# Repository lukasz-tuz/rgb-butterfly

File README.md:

# 🦋 Butterfly LED Panel: Smart Light for ESPHome

- [🦋 Butterfly LED Panel: Smart Light for ESPHome](#-butterfly-led-panel-smart-light-for-esphome)
  - [Supplies](#supplies)
  - [Concept and Design Considerations](#concept-and-design-considerations)
  - [Shaping the Butterfly](#shaping-the-butterfly)
  - [CAD](#cad)
    - [3D Modelling](#3d-modelling)
    - [Placing the LEDs](#placing-the-leds)
  - [Controller](#controller)
    - [Schematic and PCB](#schematic-and-pcb)
    - [Connectors](#connectors)
    - [Housing](#housing)
  - [Assembly](#assembly)
    - [Manufacturing](#manufacturing)
    - [Preparations](#preparations)
    - [Soldering](#soldering)
    - [Connector](#connector)
    - [Diffusing the light](#diffusing-the-light)
  - [Making The Panel Touch Sensitive](#making-the-panel-touch-sensitive)
  - [Software](#software)
    - [Substitutions](#substitutions)
    - [ESPHome configuration](#esphome-configuration)
    - [API and interfaces](#api-and-interfaces)
    - [Peripherals configuration](#peripherals-configuration)
    - [Lights](#lights)
    - [Touch controls](#touch-controls)
  - [Final Thoughts](#final-thoughts)

I've always been a fan of light panels, at least ever since I first saw
[Nanoleaf's products](https://nanoleaf.me/). My apartment has slanted walls, and
it's always been an issue to light it properly. Nanoleaf light panels got the
job done, but one place left without proper lighting: kid's bed, right
underneath a slanted wall.

At first I figured I'd just pay up and buy more light panels. But she's such a
big fan of butterflies - already had tons of stickers on that wall. Then it
struck me: I could make her a butterfly-shaped light panel to serve as a night
light. So, here goes.

## Supplies

Full bill of materials, with prices (in PLN, sorry), is attached. It includes
full BOM for PCB, including  [LCSC](https://lcsc.com/)  part numbers, estimated
prices, etc.

In addition to the PCB and its components, you'll need:
- 3D printed frame
- 3D printed case for controller
- plexi, 3 mm thick, white (laser cut is best)
- plexi, 2 mm thick, frosted (laser cut is best)
- plexi, 3 mm thick, black (laser cut is best)
- 5V 8A power supply with 2.1 mm DC jack plug
- WS2813 LED strip, 144 LED/m (different LED models can be used as well)
- Conductive PET sheet:
  https://kamami.pl/en/conductive-materials/563060-conductive-pet-ito-with-dimensions-100mm-x-200mm.html
- 4x1 Goldpin header
- DC barrel jack socket, 2.1 mm
- (optional) TE-Connectivity 1-1954289-2 connectors:
  https://www.arrow.com/en/products/1-1954289-2/te-connectivity
- some baking paper
- lots of wires, including 22AWG or similar
- general purpose glue

I estimate total cost of materials above to ~$110 USD, with the current exchange
rate.

## Concept and Design Considerations

I wanted the panel to have sections which could be individually lit to form of a
[low poly
butterfly](https://www.google.com/search?q=low+poly+butterfly&client=opera&hs=mmj&sxsrf=APq-WBtdjmTwirM-b7sVY4Ri69_1T6-vsw:1650900132022&source=lnms&tbm=isch&sa=X&ved=2ahUKEwjdtbafwq_3AhXHSvEDHZS5BSMQ_AUoAXoECAEQAw&biw=2061&bih=1141&dpr=1)
(I really like the low poly aesthetics). I also assumed use of a cut down LED
strip, to save time and money on custom PCBs, and ESP32 as a controller for the
lights, because I wanted to use  [ESPHome](https://esphome.io/)  for controlling
the lights and integrating into Home Assistant setup. I also wanted these panels
to be controllable locally (i.e., without having to use smartphone), ideally by
making the panels touch sensitive.

With these design constraints there are several options, choices to be made for
	the design: - use analogue RGB/RGBW strips vs. addressable ones - have the
	light built from multiple small panels vs. few larger ones, divided into
	segments

There are some serious cons to using analogue strips, especially given the
constrains: typical analogue LED strip needs it's own PWM driver for each
channel. This makes routing connections way more difficult and also pretty much
breaks the "save time and money on custom PCBs" assumption. Assuming use of
multiple panels, it would take a few dozen panels to create a low poly
butterfly. Total number of PWM signals would exceed number of PWM outputs in
ESP32. To mitigate, each panel would have to have its own micro-controller,
which would use a communication bus to receive commands from the controller.

In short, too complicated and bumps up the cost of each panel. Summarizing:
1.  analogue LED strip/many panels:
2.  needs custom PCB with LED drivers and separate uC per panel
3.  analogue LED strip/few panels
4.  still needs lots of LED drivers and custom PCB, slightly easier to route
    connections than 1st one
5.  addressable LEDs/many panels
6.  increased cost of 3D printing cases for panels, but only one wire needed to
    control all the LEDs
7.  addressable LEDs/few panels
8.  well... this could work.

There are so many different addressable LED strips available, it's difficult to
pick one. I decided to go with a dense strip (144 LEDs/m) based on WS2813
devices. Downside is that this strip has a rated power consumption of 43W/m. So,
a lot of current to supply at 5V...

That's how my smart light ended up having two separate panels (wings!) and
controller in the middle. But what about the low poly part? It's difficult to
get the low poly effect with just two panels. Luckily, in one of my other
projects I noticed that LED lights can be nicely partitioned. More on that
later.

## Shaping the Butterfly

For the silhouette of the butterfly, I went to trusty
[openclipart.org](http://openclipart.org/)  library. Found  [Monarch
butterfly](https://openclipart.org/detail/224784/monarch-butterfly)
cliparclip-artt, wonderful shape with decent amount of space for placing all the
LEDs. A bit of Inkscape magic, and I got the raw silhouette of a butterflies'
wing. I scaled it so that it would have diagonal of ~20 cm. I also modified the
shape a bit so that it has a distinct straight edge to which controller could
attach.

This created the outer edge of the panel. Two additional paths will be needed
later: one for marking where the internal support for panel's cover starts, and
the other is an inner edge. This can be done by cloning and shrinking the
initial shape. Best to keep approx. 2 mm of separation between the outlines.

For the whole low poly thing, I used Inkscape's Effects tool to generate a
[Voronoi diagram](https://en.wikipedia.org/wiki/Voronoi_diagram)  within the
constraints of inner edge. While low poly structures are typically composed of
triangles, this pattern gets the job done, as well.

## CAD

### 3D Modelling

Completed SVG now can be used to quickly start with 3D modelling. I'm using
[FreeCAD](https://www.freecadweb.org/), but any tool will do. You'll find
FreeCAD file in here:  https://github.com/lukasz-tuz/lowpolylight-cad.

First step is to extrude panel outline, by 3 mm, to form a back plate of the
panel. This part could be 3D printed, but I ordered it as a laser-cut white
plexiglass, opaque. It tends to be cheaper than 3D printing, and creates a
smoother shapes.

Next part is the side wall. Side wall contains a small cut, 2 mm deep, roughly
1.5 mm wide, which will be used to support front panel. That's where the inner
edges from SVG come in handy: extrude outer edge (12 mm should be enough space
to diffuse light from LEDs), extrude middle edge by 2 mm, and subtract.

Wall also should have a small cutout on a side for connecting to the controller.

Once wall is ready, it's time for the Voronoi pattern. This actually takes some
manual drawing. Pattern imported from SVG is handy, but can't be directly
extruded as all the lines are one dimensional. FreeCAD's sketching tool helps
here, but care has to be taken to ensure that the pattern overlaps with walls.
It won't be possible to print this part, otherwise.

Note the 6 mm gap between lower edge of pattern walls and back of the panel.
This way pattern walls block some of the light of LEDs inside a partition,
creating nice effect of a light segment.

Finally, front cover is created by extruding the inner edge from SVG. This part
could also be 3D printed (standard resin would do nicely), but again, I used
laser-cut plexi, 2 mm, this time with 30% opacity.

Design parts have to be cloned by mirroring to form a second wing.

### Placing the LEDs

It's all fun, 3D models for wings are ready, but how many LEDs will  *actually*
fit in there?

I wanted each segment in the Voronoi pattern generating enough light so that
this panel would be a usable light source, but at the same time, it'd be best to
try and limit current drawn by the diodes.

I ended up placing 65 LEDs per wing, and frankly, I overdid it. Whole thing
would still work with half the amount of LEDs. Oh well.

Some numbers:

- 65 LEDs per wing, total of 130 in the panel.
- with 144 LEDs per meter, 43 Watts power draw per meter, single LED consumes
  **~0.3 W at 5V**
- 130 LEDs would consume  **39 Watts**.

These numbers will be needed for the next step.

<script src="https://embed.github.com/view/3d/lukasz-tuz/rgb-butterfly/main/docs/lowpoly-butterfly.stl"></script>

## Controller

### Schematic and PCB

At first, full disclaimer: power delivery part of the controller could've (and
should've) been done better. Right now it's a very simple device, merged from
application notes for ESP32 and the voltage stabilizer.

Controller is built around ESP32 IoT module - ESP32-WROOM. These modules are
affordable, yet capable, and easy to obtain. Following typical application
circuit from ESP32-WROOM's datasheet:

- two capacitors (C5, C7; 100nF and 22uF) are filtering the 3.3V supply
- two capacitors filter the 'EN' pin; this pin is also pulled up to 3.3V by 10k
  resistor
- push button SW1 connects 'EN' pin to ground, forcing it to reset
- push button SW2 is used as boot mode selector (holding SW2 while pressing SW1
  makes the module fetch code from serial port)

Power to the module is provided by a single AMS1117-3.3 voltage stabilizer. This
device is ubiquitous, can be found on almost all low-cost development boards for
ESP. Few capacitors connect input and output of the device to ground.
AMS1117-3.3 is internally wired to output a 3.3V, so no additional resistors are
required. Input to the stabilizer comes directly from 5V power supply.

Given the power-hungriness of selected diodes, PCB traces which supply power to
the panels are pretty thick - 2 mm, with 0.8 mm min distance from other nets.
Given the current (up to 8 amps!), this net should've been even thicker, or
divided into two separate ones.

### Connectors

Given the amount of current which could potentially flow to the LEDs, connection
between controller and panels really should not be done by your run of the mill
goldpins. XST connectors typically used for LED strips would do the trick, but
are too bulky to be of use here.

Took some digging, but I finally found  [TE Connectivity
1-1954289-2](https://www.arrow.com/en/products/1-1954289-2/te-connectivity),
which is perfect for the job. 4 pins are needed:

- +5V
- ground
- LED control line
- touch sensors

Note that the cutout in panel's wall is just big enough to house this connector.

There's also a standard issue gold pin connector for serial port. Ground and
+3.3V nets are routed to that connector, so any type of USB-to-serial converter
can be used. Just make sure to not connect +5V to the +3.3V pin of the serial
port header. ESP32 will probably survive but no point in taking chances.

> However, soldering wires instead using some exotic connector will work just as
> fine.

### Housing

Now, back to drawing board. Err, CAD. Controller can't just hang there between
the panels, it needs a casing. Since - as usual - I rushed PCB design and forgot
about mounting holes, I decided to design a very simple 3D printed case in which
the PCB would rest, held in place by connectors. Cover for the case is laser cut
plexi, black this time, in shape of butterfly's body. Cover is wider and longer
than the case itself, so it hides all connectors.

Case has also small rectangular cutouts in which case fits. Cutouts are slightly
(0.1 mm) smaller in each direction than the mounting pins on the case, so it
doesn't really need any glue or screws.

## Assembly

### Manufacturing

I ordered the laser-cut and 3D-printed parts at
[ajmaker.pl](http://ajmaker.pl/), they offer good quality with reasonable prices
(and I am not affiliated with them in any way, I just buy stuff from them :)).

Note on 3D printing the side wall/Voronoi pattern: make sure to use material
with the highest temperature resistance you can find. LEDs can get hot!

Controller's PCB (including SMT assembly) was made by
[JLCPCB](https://www.jlcpcb.com/see), I highly recommend their services. It's
super easy to place the order using their online interface - just add gerber
files (live preview!), select options for the PCB - base material, number of
layers, color (purple PCB, anyone?), thickness, etc. - add to cart and done. If
anything's wrong or not clear, their engineers will contact you to resolve
things. SMT service is great as well. Lots and lots of parts in stock so it's
easy to find matching devices.

Once all the parts arrive, it's time for some assembly.

### Preparations

First step here is to cut the LED strip into fragments matching the CAD design
and arrange them on the back plate of the panel. When arranging, make sure that
LED strip fragments are arranged so that ground and power supply pins are next
to each other in adjacent fragments. Otherwise laying down the wires will get
complicated. Fragments of the LED strip can be glued to the back plate at this
point, it'll make soldering bit easier later on.

### Soldering

Even though its cut down, it still is a LED strip. Addressable LEDs use just one
wire (in case of WS2813 diodes I used - two wires, additional wire serves as
backup) for control, but all devices need to be connected in chain on the same
wire. So, it is important arrange and solder all the LED fragments as a chain,
avoiding any loops. At least on the control pins.

For connecting power and ground pins of LED strip fragments I used standard
22AWG wire ([this
one](https://thepihut.com/products/prototyping-wire-spool-set), to be exact).
Soldering it to the LED strip was sometimes bit difficult, but at least it can
withstand high current and not melt... It's also pretty rigid, so it also helps
to keep all the LED strip pieces in desired places.

For signal lines, any wire will do. I used thin wire stripped off from a tape;
easy to work with and easy to solder.

### Connector

Once all the LEDs are in place and all the wires are soldered, it's time for the
connector. TE part I picked is meant for SMT soldering, but it has large pads.
It's super easy to solder wires to it. Make sure you're soldering them in the
right order: power supply and ground on the outer pins, signal lines on the
inner.

I found (by trial and error, obviously) that using more elastic wires for
power/ground than 22AWG makes it easier to assemble everything later on.

One of the signal pins needs to be connected to the LEDs, the other should be
left dangling for the touch sensor. I left around 5-7 cm piece of wire with
approx. 1 cm with removed isolation. This wire is supposed to connect to a
conductive layer (added in next steps) to form a touch sensor.

At this point it should be safe to assemble back plate with the wall/partition
part. I used general purpose glue based on polyurethane-elastomers. It's
transparent, creates an elastic bond, and does not dry immediately which gives
an opportunity for adjusting alignment of parts. Also, as it turns out, if you
need to disassemble a glued part, just cut through the glue with a scalpel,
scrub out remains of the old bond, and glue again.

> I do not recommend using cyanoacrylate-based glues (e.g., Super Glue). They
> can dissolve 3D-printed parts.

### Diffusing the light

Front of the panel is made of frosted, 30% opacity Plexiglas, which diffuses the
light on its own. First startups of an assembled panel show, however, that the
diffusion effect is not strong enough.

There's a boatload of guides on the internet on how to diffuse light of a LEDs.
After some experimenting with what I had on hand, I went with baking paper. It
can easily be cut to desired shape, diffuses the light nicely, and is heat
resistant (which is good, because the diodes can get quite hot). So, cut two
butterfly wing-shaped pieces out of baking paper sheet (use front panel part as
template), and place them on the walls of the Voronoi pattern part. Just that,
no need to glue it, pin it, or anything. Front plexi will go on top of it and
will hold it down in place.

## Making The Panel Touch Sensitive

Remember the dangling wire soldered to wing connectors? Now it's time to put it
to work.

My first approach was to use  [conductive
paint](https://www.bareconductive.com/)  to paint the Voronoi pattern on top of
the front plexi. Idea was that loose end of the wire would be painted over and
held in place by the paint. That did not work because conductive paint does not
stick to plexi. I used paper tape to mask the lines and when I pulled the tape
off, conductive paint decided to stick with the tape rather than the panel.

Second approach, was to use silver adhesive, conductive tape to lay out Voronoi
pattern on top of the front cover. Touch sensor wire would be connected outside
of the panel, but simply one of the pattern's edges extended to inner side of
the front cover, where it was wrapped over the touch sensor wire.

This was a limited success (see video above); touch controls worked, but there
were constant problems with maintaining electrical connection between segments
in the pattern. Also, visual effect wasn't exactly what I hoped it would be.

So after some digging around the interwebs I found transparent,  [conductive
plastic
sheet](https://kamami.pl/en/conductive-materials/563060-conductive-pet-ito-with-dimensions-100mm-x-200mm.html).
It's easy to cut and provides additional diffusion of light. Once cut, can
simply be placed on top of the baking paper, err.. light diffuser. Stripped
fragment of the touch sensor wire should be placed on top of the conductive
layer (can be taped, but I didn't bother), and front cover placed directly on it
and glued to the walls.

And that's it, panel is now touch sensitive.

## Software

Software for the controller is built on top of the
[ESPHome](https://esphome.io/)  framework. Everything is captured in a short
YAML configuration file. Let's go over each section of the configuration.

### [Substitutions](https://esphome.io/guides/configuration-types.html?highlight=substitutions#substitutions)

```yaml
substitutions:
  name: "kids-room-bedlight"
  num_leds: '66'
  max_led_idx: '65'
  gamma_correct: '1.5' 
```

These definitions hold values which are use in several places throughout the
configuration. To make it easier to tweak those values, it's good to have them
defined in one place. Basic, run-of-the-mill constants for:

- *name*: name of the device which will be used as host name, as well as Home
  Assistant entity for the light. Here it's "Kid's room bed light" because
  that's where the panel will be placed
- *num_leds*: total number of LED diodes in the device
- *max\_led\_idx*: highest value for zero-based index of LED. Has to equal to
  *num_leds*  \- 1
- *gamma_correct*: gamma correction factor applied to lights

### ESPHome configuration

```yaml
esphome:
  name: ${name}
  project:
    name: "hexalight.lowpoly-butterfly"
    version: "1.0.0"

esp32:
  board: esp32dev
  framework:
    type: arduino

# Enable logging
logger: 
```

This section contains basic configuration of the  [ESPHome framework
itself](https://esphome.io/devices/esp32.html). See how previously defined
device name is used, using `${name}` syntax?

Project section allows for defining manufacturer (yeah, I know :D) and model
name, as well as version.

"esp32" defines values needed for [PlatformIO](https://platformio.org/)
framework on which ESPHome is built upon. Selects board type and low-level
firmware framework - operating system and set of libraries to use. In this case,
Arduino is used to fuel the code.

### API and interfaces

```yaml
# Enable Home Assistant API
api:

ota:
  password: !secret ota_password

wifi:
  ssid: !secret wifi_ssid
  password: !secret wifi_password

# Enable fallback hotspot (captive portal) in case wifi connection fails
ap:
  ssid: "Lowpoly-Butterfly"
  password: !secret ap_password

captive_portal:
```

This part enables ESPHome awesomeness:

- *api*: adds support for the  [Home Assistant](https://www.home-assistant.io/)
  interface, making the device magically appear in the home automation
- *ota*: enables Over-the-air firmware updates. Only first programming needs to
  be done using serial interface, any subsequent update will go through Wi-Fi
- *wifi*: turns on Wi-Fi stack, allowing the device to connect to network
  specified by  *ssid*  using provided  *password*
- *ap:* enables fallback hotspot, AKA captive portal. If connection to selected
  network fails, device will set up its own hotspot, using  *ssid*  and
  *password*  provided here
- *captive_portal*: (requires enabled access point); when Wi-Fi connection
  fails, device will display a web page to re-configure Wi-Fi
- *web_server*: (optional) when enabled, device will be accessible using web
  interface, allowing for remote control even without Home Assistant setup
- *esp32_improv*: (optional) when enabled, device will use ESPHome
  implementation of the  [Improv](https://www.improv-wifi.com/)  standard to
  provision ssid and password. So, no need to type them in configuration file.

Notice the "*!secret some_password*" syntax in all the places which require
providing a password. Using the "*!secret*" tag, ESPHome scripts refer to a
separate file - secrets.yaml - to look for the password. This way ESPHome config
files can be shared over the internat without exposing passwords to own Wi-Fi.
Of course that's assuming you don't file the secrets.yaml...

### Peripherals configuration

Now, configuration of ESP32's peripherals.

```yaml
switch:
- platform: restart
  name: "Restart Light" 
```

This part defines a virtual  [reset
button](https://esphome.io/components/switch/restart.html). Switch will be
visible as an entity in Home Assistant and web interface (if enabled).

- esp32\_touch: setup\_mode: false iir\_filter: 15ms low\_voltage\_reference:
  0.5V high\_voltage\_reference: 2.7V voltage\_attenuation: 1.5V
- '*esp32_touch*' enables code for  [touch sensor
  pads](https://docs.espressif.com/projects/esp-idf/en/latest/esp32/api-reference/peripherals/touch_pad.html)
  built into the ESP32 device. ESP32's touch pad peripheral continuously charges
  and discharges the touch pad (in this case - the conductive plastic sheet
  under front cover). Changes in the charge/discharge timings indicate change of
  capacity of the touch pad. And capacity of the touch pad changes when it is
  touched.
- *setup_mode*: when set to true, touch pad is in setup mode, in which results
  of the touch pad measurements are periodically printed out to the log. Useful
  when building the device, because it makes calibration of the touch pad super
  easy
- *iir_filter*: enables  [Infinite Impulse
  Response](https://en.wikipedia.org/wiki/Infinite_impulse_response)  filter to
  be applied to the touch pads. Can increase accuracy, and turned out to be
  helpful for making the touch panel work
- *low\_voltage\_reference*,  *high\_voltage\_reference*: reference values for
  voltage used by ESP32 touch pad subsystem to analyze the charge/discharge
  pattern. Used to tune the performance of touch panel
- *voltage_attenuation*: value of the voltage attenuation to use for the charge
  cycles. Based on my observations, increasing this value increases resolution
  of the touch pad, making it easier to determine a threshold for on/off values

### Lights

As probably expected, configurations related to LEDs themselves consumes most of
the configuration file. Let's go over it in steps.

```yaml
light:
  - platform: fastled_clockless
    gamma_correct: ${gamma_correct}
    restore_mode: ALWAYS_OFF
    rgb_order: GRB
    chipset: WS2813
    pin: GPIO22
    num_leds: ${num_leds}
    name: "Right Wing"
    id: right_wing
    internal: true

- platform: neopixelbus
  gamma_correct: ${gamma_correct}
  restore_mode: ALWAYS_OFF
  type: GRB
  variant: WS2813
  pin: GPIO23
  num_leds: ${num_leds}
  name: "Left Wing"
  id: left_wing
  internal: true 
```

First, we have to define low-level libraries to interact with LEDs. These map to
physical layout of the diodes. Note that two different libraries are used:
[FastLED Clockless](https://esphome.io/components/light/fastled.html)  and
[Neopixelbus](https://esphome.io/components/light/neopixelbus.html). These
libraries provide similar set of features to control addressable LEDs. Two
different are used because code wouldn't compile when the same library was used
for two separate sets of lights. Probably something related to use of global
variables, but I wasn't really inclined to debug this; perhaps another day. For
now, one library is used for left wing, the other for right wing.

Both libraries have a very similar set of configuration options:

- *platform*:  *fastled_clockless*  or  *nexopixelbus*  selects underlying
  library to use for the light entity
- *gamma_correct*: gamma correction factor to apply to this light
- *restore_mode*: defines how light should behave on power up. ALWAYS_OFF is a
  safe bet to make sure light won't randomly turn on when power comes back from
  outage or when the devices encounters a software bug and resets in the middle
  of the night
- *rgb_order*  or  *type*: defines order in which colors in LED are to be
  defined; if defined incorrectly, configuration will not match actual color
  channel, and setting values for red would change another color in the LED.
- *chipset*  or  *variant*: select model of the RGB LED diode used in the LED
  strip
- *pin*: pin in ESP32 module to which LED strip is connected
- *num_leds*: number of LEDs in connected to selected pin
- *name*: (optional) name for this light; typically, that's the name that would
  be displayed in Home Assistant
- *id*: unique identifier for the light used within the code
- *internal*: set to true means that this light will not be exposed externally,
  in Home Assistant or web interface

Logical definition uses  [ESPHome's light
partition](https://esphome.io/components/light/partition.html)  feature which
allows for merging several physical lights into single, controllable light
entity (it also allows for splitting a single physical light into several
logical ones).

Some options are common to all light entities (*name*,  *id*,  *restore_mode*,
...), so let's skip them here.

- *segments*: definition of segments used by this partition. Defines which
  physical lights and which LEDs in those lights should be used for the
  partition. Here, all diodes from both wings are selectd
- *id*: identifier of physical light
- *from*  and  *to*: range of LED  indices  to use for the segment
- *effects*: defines list of light effects (also known as scenes, animations,
  etc.) for the logical light entity
- *addressable_lambda*: uses  [*lambda
  expression*](https://en.cppreference.com/w/cpp/language/lambda)  for
  definition of an effect
- *name*: name of the effect
- *update_interval*: defines how often should the lambda expression be executed
- *lambda*: body of the lambda expression
- *addressable_rainbow*: creates effect of a floating rainbow by cycling through
  entire RGB space on each LED
- *addressable_twinkle*: randomly twinkles individual diodes, creating effect of
  blinking stars

Some effects are defined by raw C++ code. The "Reading Light" effect is simple.

```c
  it.all()= Color(255, 170, 160);
  return;
```

This sets all diodes to a specific color. I picked this color because it's easy
on the eyes, bit pinkish, and reduces strain when reading. "Voronoi" effect is
more complex. I wanted an effect which lights up each partition in the Voronoi
pattern individually, and smoothly transitions colors for each of the partition.
Also wanted to make sure that colors used will resemble an actual  [monarch
butterfly](https://www.google.com/search?client=opera&q=monarch+butterfly).
Lambda expression for this effect is evaluated every 1 ms.

```c++
  #define INT_TO_FIXED16(n) (n << 8)
  static const uint8_t nsegments = 18;
  static const uint8_t speed = 2;

  // Count of LEDs in each of the segments
  static const uint8_t segments[nsegments] = {6, 6, 5, 12, 2, 13, 3, 4, 5,\
                                              7, 6, 5, 12, 2, 13, 5, 4, 3};
  static uint16_t colors[nsegments];
  
  static const uint16_t min_hue = INT_TO_FIXED16(142);
  static const uint16_t hue_range = INT_TO_FIXED16(81);
  static const uint16_t max_hue = min_hue + hue_range;
```

Note how all the configuration constants/variables are defined as  *static*.
This keyword makes these variables persistent over subsequent evaluations.
Values set to those variables in one evaluation are kept for the next one.

```c++
  if (initial_run) {
    for (int i = 0; i < nsegments; i++) {
      // Initialize to a random color
      colors[i] = (uint16_t)(random_uint32() & 0x0000FFFF);
    }
  }
```

This code generates random target color for each partition (AKA segment) in the
Voronoi pattern.

```c++
  ESPHSVColor hsv(0, 240, 255);
  uint16_t start = 0;
  for (uint8_t i = 0; i < nsegments; i++) {
    uint16_t end = start + segments[i] + 1;
    colors[i] = (colors[i] + speed) % 0xFFFF;
    hsv.hue = (colors[i] >> 8) & 0xFF;
    it.range(start, end) = hsv.to_rgb();
    start = end;
  }
  return;
```

And finally, loop that makes gradual color transition for each partition.

### Touch controls

Touch pad controls use  [binary sensor implementation in
ESPHome](https://esphome.io/components/binary_sensor/esp32_touch.html).

```yaml
  binary_sensor:
  - platform: esp32_touch
    name: "On/Off"
    pin: GPIO32
    threshold: 1150
    filters:
      - delayed_on_off: 50ms
    on_click:
      - min_length: 800ms
        max_length: 5000ms
        then:
          - light.turn_off: lowpoly
      - min_length: 50ms
        max_length: 700ms
        then:
          lambda: |-
             ... 
```

- *platform*: defines which physical peripheral should be used for the sensor;
  here it's '*esp32_touch*'
- *name*: name of the switch which will be used in Home Assistant/web interface
- *pin*: physical GPIO which is used by the sensor. This corresponds to GPIO to
  which the touch sensor wire is connected
- *threshold*: ESP32 touch pad peripheral returns integer values; the lower the
  value, the higher probability that touch pad was touched. Binary sensor will
  change the state to 'On' when readings from the touch pad drop below the
  *threshold*  defined here
- *filters*: defines filters to use for raw values incoming from the hardware
- *delayed\_on\_off*: creates a slight delay between publishing any state change
  ('Off' to 'On' or  *vice versa*). Useful for filtering noise in readings from
  the touch pad
- *on_click*: defines behavior of the touch pad when touched
- *min_length*  and  *max_length*: specify duration of time touch pad needs to
  be activated before taking an action
- *then*: defines action to be taken

Code here implements two modes of operation:

- when "On/Off" panel (left wing) is touched for anywhere between 800 and 5000
  ms, light is turned off by invoking action: `light.turn_off: lowpoly`
- when "On/Off" panel is touched for a shorter time (50 - 700 ms), action
  defined by lambda is taken

```c++
  static const int levels = 5;
  static const float brightness_levels[levels] = {0.0, 0.15, 0.45, 0.8, 1.0};
  
  static int current_level = 0;
  
  current_level = (current_level + 1) % (levels);
  
  auto effects = id(lowpoly).get_effects();
  std::string effect_name = id(lowpoly).get_effect_name();
  if (effect_name == "None") {
  	effect_name = effects.front()->get_name();
  }
  
  if (current_level > 0) {
      auto call = id(lowpoly).turn_on();
      float brightness = brightness_levels[current_level];
      call.set_brightness(brightness);
      call.set_effect(effect_name);
      call.perform();
  }
  else {
   	auto call = id(lowpoly).turn_off();
   	call.perform();
  }
  return; 
```

This action makes the light cycle through specific brightness levels, while
maintaining activated effect. Each touch will make the light go to 15%, 45%,
80%, 100%, and 0% (lights off) of the brightness. For the right wing,
configuration is similar:

```yaml
  - platform: esp32_touch
   name: "Toggle Effect"
   pin: GPIO33
   threshold: 1050
   filters:
    - delayed_on_off: 100ms
   on_click:
    - min_length: 800ms
      max_length: 5000ms
      then:
        - light.turn_off: lowpoly
    - min_length: 50ms
      max_length: 700ms
      then:
        lambda: |-
          ... 
```

Long touch will turn the light off, short will activate a lambda which cycles
through defined light effects:

```c++
  auto call = id(lowpoly).turn_on();
  auto effects = id(lowpoly).get_effects();
  std::string name = id(lowpoly).get_effect_name();
  uint8_t i = 0;
  if (name != "None") {
  	// There's an effect in progress, move to the next one
  	for (auto e : effects) {
  		++i %= effects.size();
  		if (e->get_name() == name) {
  			break;
  		}
  	}
  }
  call.set_effect(effects[i]->get_name());
  call.perform();
  return; 
  - 10)
```

And that's it! Compile and upload using ESPHome, and the butterfly light panel
should light up.

## Final Thoughts

There are definitely some improvements to be had with this design:

- overhaul the power delivery part of the controller
- see if placing the LEDs vertically along the edges of Voronoi pattern would
  improve light diffusion effect
- make the touch panels more robust

Still, I'm super happy with the result. Maybe next version of the panels will
see those improvements. I still have a slanted wall with no reading light in my
own bedroom...

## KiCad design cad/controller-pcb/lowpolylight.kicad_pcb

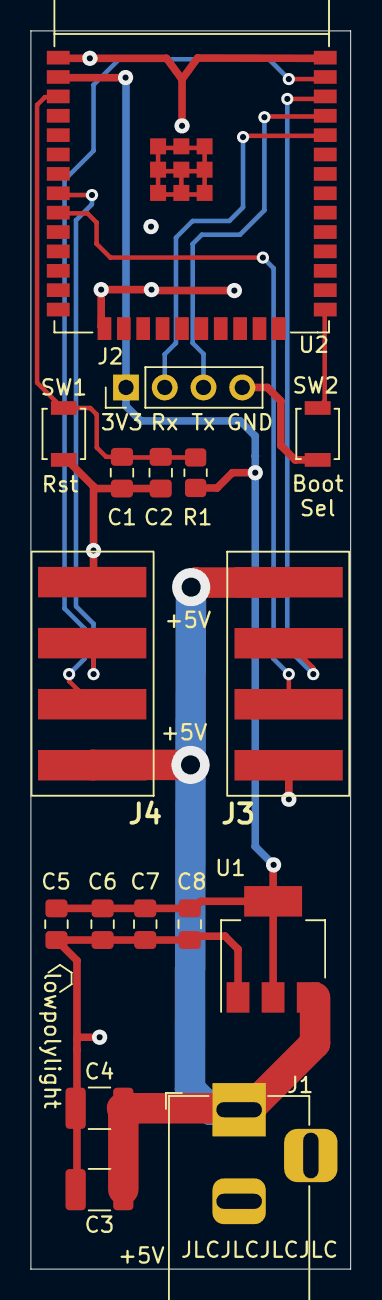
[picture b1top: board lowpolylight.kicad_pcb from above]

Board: 2 copper layers, 21.0 x 81.2 mm, 17 parts (0 on the bottom side), 11 nets.

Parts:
C1, C5, C6: 100nF; C_0805_2012Metric_Pad1.18x1.45mm_HandSolder
C2: 1uF; C_0805_2012Metric_Pad1.18x1.45mm_HandSolder
C3: 22uF; C_1210_3225Metric_Pad1.33x2.70mm_HandSolder
C4: 100nF; C_1210_3225Metric_Pad1.33x2.70mm_HandSolder
C7, C8: 22uF; C_0805_2012Metric_Pad1.18x1.45mm_HandSolder
J1: Conn_Coaxial_Power; BarrelJack_Horizontal
J2: Serial; PinHeader_1x04_P2.54mm_Vertical
J3: Right Panel; 119542892
J4: Left Panel; 119542892
R1: 10k; R_0805_2012Metric_Pad1.20x1.40mm_HandSolder
SW1: Reset; SW_SPST_B3U-1000P
SW2: Boot Option; SW_SPST_B3U-1000P
U1: AMS1117-3.3; SOT-223-3_TabPin2
U2: ESP32-WROOM-32E

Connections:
+3V3: C5.2, C6.1, C7.2, C8.1, J2.1, R1.1, U1.2 (VO), U2.2 (3V3)
+5V: C3.1, C4.1, J1.1 (In), J3.1, J4.1, U1.3 (VI)
/RST: C1.2, C2.2, R1.2, SW1.2, U2.3 (EN/CHIP_PU)
/Rx: J2.2, U2.34 (U0RXD/GPIO3)
/Tx: J2.3, U2.35 (U0TXD/GPIO1)
GND: C1.1, C2.1, C3.2, C4.2, C5.1, C6.2, C7.1, C8.2, J1.2 (Ext), J2.4, J3.4, J4.4, SW1.1, SW2.1, U1.1 (GND), U2.1 (GND), U2.15 (GND), U2.38 (GND)
LED_L: J4.2, U2.37 (GPIO23)
LED_R: J3.2, U2.36 (GPIO22)
unnamed: SW2.2, U2.25 (GPIO0/BOOT/ADC2_CH1)
TOUCH_L: J4.3, U2.8 (32K_XP/GPIO32/ADC1_CH4)
TOUCH_R: J3.3, U2.9 (32K_XN/GPIO33/ADC1_CH5)

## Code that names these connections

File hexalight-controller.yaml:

substitutions:
  name: "kids-room-bedlight"
  num_leds: '66'
  max_led_idx: '65'
  gamma_correct: '1.5'

esphome:
  name: ${name}
  project:
    name: "hexalight.lowpoly-butterfly"
    version: "1.0.0"

esp32:
  board: esp32dev
  framework:
    type: arduino

# Enable logging
logger:

# Enable Home Assistant API
api:

ota:
  password: !secret ota_password

wifi:
  ssid: !secret wifi_ssid
  password: !secret wifi_password

  # Enable fallback hotspot (captive portal) in case wifi connection fails
  ap:
    ssid: "Lowpoly-Butterfly"
    password: "SsBQuDL3bOYV"

captive_portal:

# web_server:
#   port: 80

switch:
  - platform: restart
    name: "Restart Light"

# esp32_improv:
#   authorizer: none

light:
  - platform: partition
    name: ${name}
    id: lowpoly
    restore_mode: ALWAYS_OFF
    gamma_correct: ${gamma_correct}
    segments:
      - id: right_wing
        from: 0
        to: ${max_led_idx}
      - id: left_wing
        from: 0
        to: ${max_led_idx}
    effects:
      - addressable_lambda:
          name: "Reading Light"
          update_interval: 1s
          lambda: |-
            it.all()= Color(255, 170, 160);
            return;
      - addressable_rainbow:
          name: "Rainbow"
          width: ${num_leds}
      - addressable_twinkle:
          name: "Twinkle"
      - addressable_lambda:
          name: "Voronoi"
          update_interval: 1ms
          lambda: |-
            // Time, in miliseconds, needed for each segment to transition to new random color
            static const uint16_t segtrans = 200;

            // Number of segments
            static const uint8_t nsegments = 18;

            // End indices for each segment
            static const uint8_t ranges[nsegments] = {7, 14, 20, 33, 36, 50, 54, 59, 65, \
                                                      72, 79, 85, 98, 101, 115, 119, 124, 131};

            // Number of steps in each transition
            static const uint16_t steps = segtrans / 1;

            static uint16_t progress = 1;

            // Base, starting color
            static uint8_t start_colors[nsegments] = {127};
            static uint8_t target_colors[nsegments] = {0};

            static float segcolors[nsegments] = {0};

            if (initial_run || progress == steps) {
              // Generate random new target color for each segment
              random_bytes(target_colors, nsegments);
              // Clip values
              for (uint8_t ii = 0; ii < nsegments; ii++) {
                target_colors[ii] = min(target_colors[ii], (uint8_t)164);
              }
              progress = 1;
            }

            uint8_t start = 0;
            uint8_t end = 0;

            for(uint8_t ii = 0; ii < nsegments; ii++) {
              end = ranges[ii] + 1;
              float k = (float)(target_colors[ii] - start_colors[ii]) / (float)steps;
              segcolors[ii] = start_colors[ii] + k * progress;
              it.range(start, end) = Color(220, (uint8_t)segcolors[ii], 0);
              start = end;
            }
            progress++;

            if (progress == steps) {
              memcpy(start_colors, target_colors, nsegments);
            }

            return;

  - platform: fastled_clockless
    gamma_correct: ${gamma_correct}
    restore_mode: ALWAYS_OFF
    rgb_order: GRB
    chipset: WS2813
    pin: GPIO22
    num_leds: ${num_leds}
    name: "Right Wing"
    id: right_wing
    internal: true

  - platform: neopixelbus
    gamma_correct: ${gamma_correct}
    restore_mode: ALWAYS_OFF
    type: GRB
    variant: WS2813
    pin: GPIO23
    num_leds: ${num_leds}
    name: "Left Wing"
    id: left_wing
    internal: true

esp32_touch:
  setup_mode: false
  iir_filter: 15ms
  low_voltage_reference: 0.5V
  high_voltage_reference: 2.7V
  voltage_attenuation: 1.5V

binary_sensor:
  - platform: esp32_touch
    name: "On/Off"
    pin: GPIO32
    threshold: 1100
    filters:
      - delayed_on_off: 100ms
    on_click:
      - min_length: 800ms
        max_length: 5000ms
        then:
          - light.turn_off: lowpoly
      - min_length: 100ms
        max_length: 700ms
        then:
          lambda: |-
            static const int levels = 5;
            static const float brightness_levels[levels] = {0.0, 0.5, 0.65, 0.8, 1.0};

            static int current_level = 0;

            current_level = (current_level + 1) % (levels);

            auto effects = id(lowpoly).get_effects();
            std::string effect_name = id(lowpoly).get_effect_name();
            if (effect_name == "None") {
              effect_name = effects.front()->get_name();
            }

            if (current_level > 0) {
              auto call = id(lowpoly).turn_on();
              float brightness = brightness_levels[current_level];
              call.set_brightness(brightness);
              call.set_effect(effect_name);
              call.perform();
            }
            else {
              auto call = id(lowpoly).turn_off();
              call.perform();
            }
            return;

  - platform: esp32_touch
    name: "Toggle Effect"
    pin: GPIO33
    threshold: 1050
    filters:
      - delayed_on_off: 100ms
    on_release:
      then:
        lambda: |-
            auto call = id(lowpoly).turn_on();

            auto effects = id(lowpoly).get_effects();
            std::string name = id(lowpoly).get_effect_name();

            uint8_t i = 0;

            if (name != "None") {
              // There's an effect in progress, move to the next one
              for (auto e : effects) {
                ++i %= effects.size();
                if (e->get_name() == name) {
                  break;
                }
              }
            }

            call.set_effect(effects[i]->get_name());
            call.perform();
            return;

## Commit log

2022-02-09 gitignore settings for ESPhome projects
2022-03-06 First version of a voronoi effect
2022-03-06 Adding effect toggle handler
2022-03-06 Tuning the voronoi effect
2022-03-13 Removing unused constant
2022-03-13 Creating light partition from two wings
2022-03-13 Restart and on/off switches
2022-03-16 Adjustments in voronoi effect
2022-03-20 re-enabling touch controls
2022-03-26 Tuning touch pads and effects
2022-04-01 Adding brightness toggle behavior
2022-04-16 Adding reading light effect, tuning gamma
2022-04-16 brightness button only triggers effects
2022-04-16 Change restore mode to always off
2022-04-16 Rearranging effects
2022-04-16 Long press turns light off
2022-04-18 reconfiguring node name
2022-04-24 Tuning touch threshold, adding name subsitutions
2022-05-02 Repo cleanup, name change
2022-05-02 Updating README
2023-10-21 Rewriting custom effects
2023-10-25 Final touches to v 1.1
2023-10-25 Merging content from obsoleted repos
